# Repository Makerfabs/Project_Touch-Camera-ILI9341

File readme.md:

# Touch Screen Camera ILI9341

```c++
/*
Version:		V1.4
Author:			Vincent
Create Date:	2020/9/28
Note:
		V1.1:Add Screen Shot Receiver Function.
		V1.2:Add a faster camera example.
		2020/12/2 v1.3:Add album and a meter display.
		2020/12/28 v1.4: Add camera_faster_v2.
	
*/
```

[toc]

# OVERVIEW

## Introduce

[Makerfabs home page](https://www.makerfabs.com/)

[Makerfabs Wiki](https://wiki.makerfabs.com/)

The realization of a simple digital camera, you can take pictures through the camera framing. It is displayed on the TFT screen and provides touch options. Photos taken can be saved on an SD card.

The ILI9341 screen has more adaptation libraries. Such as Adafruit_GFX, Adafriut_ILI9341, TFT_eSPI and other libraries. The resistance screen is driven by Adafruit_STMPE610 library. Fully compatible with Adafruit products.

## Equipment list

- ESP32 Touch Camera ILI9341
- Micro SD card

# ESP32 Touch Camera

## Product link ：[ESP32 3.2" TFT Touch with Camera](https://www.makerfabs.com/esp32-3.2-inch-tft-touch-with-camera.html) 

The ESP32 Touch Camera ILI9341 use ILI9341 screen, which comes with resistive screens. Have an OV2640 camera and SD card slot. It can be used as a webcam, an electronic album, or a digital camera. Support for Arduino and MicroPython. 

## Feature

- Integrated ESP32 2.4G WiFi and Bluetooth.
- Micro SD card slot on board.
- Input 5.0V Type-C USB .
- OV2640 is a 1/4 inch CMOS UXGA (1632*1232) image sensor manufactured by OmniVision.
- LCD 3.2 inch Amorphous-TFT-LCD (Thin Film Transistor Liquid Crystal Display) for mobile-phone or handy electrical equipments. The resolution is 320*240.
- STMPE610 is A 4-wire resistive touch screen control circuit with I2C interface and SPI interface.

# Example

## Camera

This is a test demo. You can check that ESP32, screen, touch, SD card reader and the camera function properly.

- Copy logo.bmp to sd card.
- Insert SD card.
- Upload code to ESP32.
- Restart ESP32.
- Screen will show "TOUCH TO START TEST", please touch screen.
- Will show logo picture in SD card.
- And ESP32 will open camera, and show on screen.

### Camera_faster_v2

Use LovyanGFX library. More faster than Adafruit_GFX. This example don't need SD card.
- Upload code to ESP32.
- Copy logo320240.bmp to sd card.
- Insert SD card.
- Restart ESP32.
- Screen will show "TOUCH TO START TEST", please touch screen.
- And ESP32 will open camera, and show on screen.

## Example introduction

Five projects were implemented : "Graphic_Test", "Touch_Test", "Touch_Draw", "SD_Test" and "Wifi_Camera".

### Graphic_Test

- Test ILI9341 screen with Adafruit_ILI9341 library.

### Touch_Draw

- Test ILI9341 screen with Adafruit_STMPE610 library.

### Touch_Draw

- Use your hand or stylus (resistance screen) to draw on the screen.

### SD_Test

- Display pictures from SD card.

### Wifi_Camera

- Use esp32 and ov2640 as a webcam.
- Provides a real-time display of the control web page.

### Screen Shot Receiver

Transmit the contents of the monitor to the TFT screen via Wifi.A host computer software is provided to box select the areas of the screen that need to be transferred.

Change from [MakePython ESP32 Color LCD で 動画をWiFi受信](https://homemadegarbage.com/makerfabs05)

- Upload codes.

- Open "ScreenShotSender.exe"

- Input IP on the screen.

- Click "Connect"

  `
### Album

Read JPG image from SD card and display it on screen.You can switch photos by clicking on the left or right side of the screen.For the sake of display, it is best not to be larger than 320 * 240 pixels.
- Copy the image from the JPG folder to the SD root directory.
- Insert SD card.
- Upload code to ESP32.
- Restart ESP32.
- Will show jpg picture in SD card.

## Compiler Options

**If you have any questions，such as how to install the development board, how to download the code, how to install the library. Please refer to :[Makerfabs_FAQ](https://github.com/Makerfabs/Makerfabs_FAQ)**

- Install board : ESP32 .
- Install library : Adafruit_GFX library.
- Install library : Adafruit_ILI9341 library.
- Install library : Adafruit_STMPE610 library.

- Insert a Micro SD card into ESP32 Touch Camera.
- Upload codes, select "ESP32 Wrover Module" and "Huge APP"

## Code Explain

- Import Library

```c++
#include "SPI.h"
#include "SD.h"
#include "FS.h"
#include "Adafruit_STMPE610.h"
#include "Adafruit_GFX.h"
#include "Adafruit_ILI9341.h"
```

- Define Pins

```c++
//SPI
#define SPI_MOSI 13
#define SPI_MISO 12
#define SPI_SCK 14

//SD Card
#define SD_CS 4

//Touch Screen
#define STMPE_CS 2

//TFT
#define TFT_CS 15
#define TFT_DC 33
#define TFT_LED -1 //1//-1
#define TFT_RST -1 //3//-1
```

- Set Cs function. Because the screen, touch and SD card all use SPI interface. To prevent SPI conflicts, the manual SPI switch is set. Low is enable.

```c++
//SPI control
#define SPI_ON_TFT digitalWrite(TFT_CS, LOW)
#define SPI_OFF_TFT digitalWrite(TFT_CS, HIGH)
#define SPI_ON_SD digitalWrite(SD_CS, LOW)
#define SPI_OFF_SD digitalWrite(SD_CS, HIGH)
#define STMPE_ON digitalWrite(STMPE_CS, LOW)
#define STMPE_OFF digitalWrite(STMPE_CS, HIGH)
```

- Init SPI

```c++
SPI.begin(SPI_SCK, SPI_MISO, SPI_MOSI);
```

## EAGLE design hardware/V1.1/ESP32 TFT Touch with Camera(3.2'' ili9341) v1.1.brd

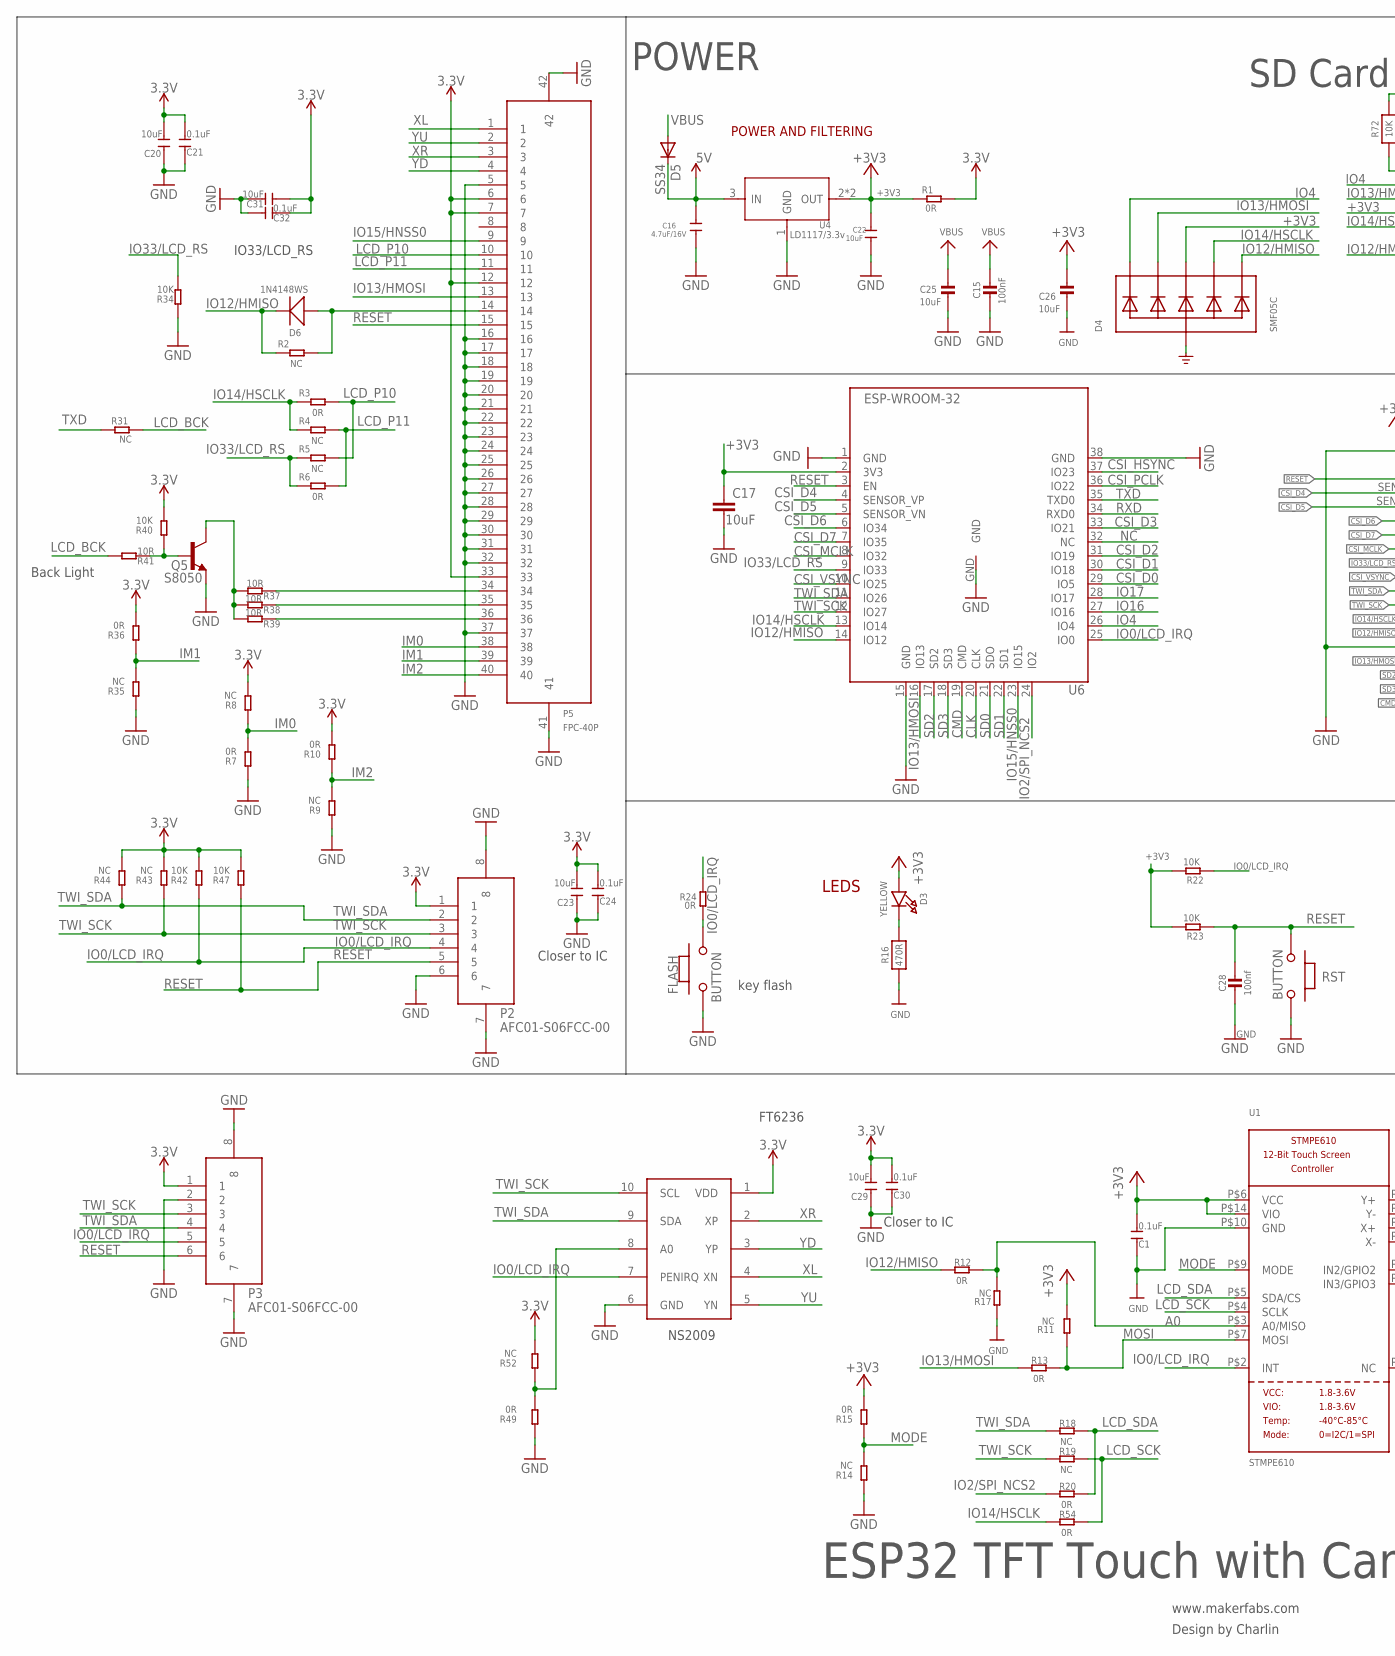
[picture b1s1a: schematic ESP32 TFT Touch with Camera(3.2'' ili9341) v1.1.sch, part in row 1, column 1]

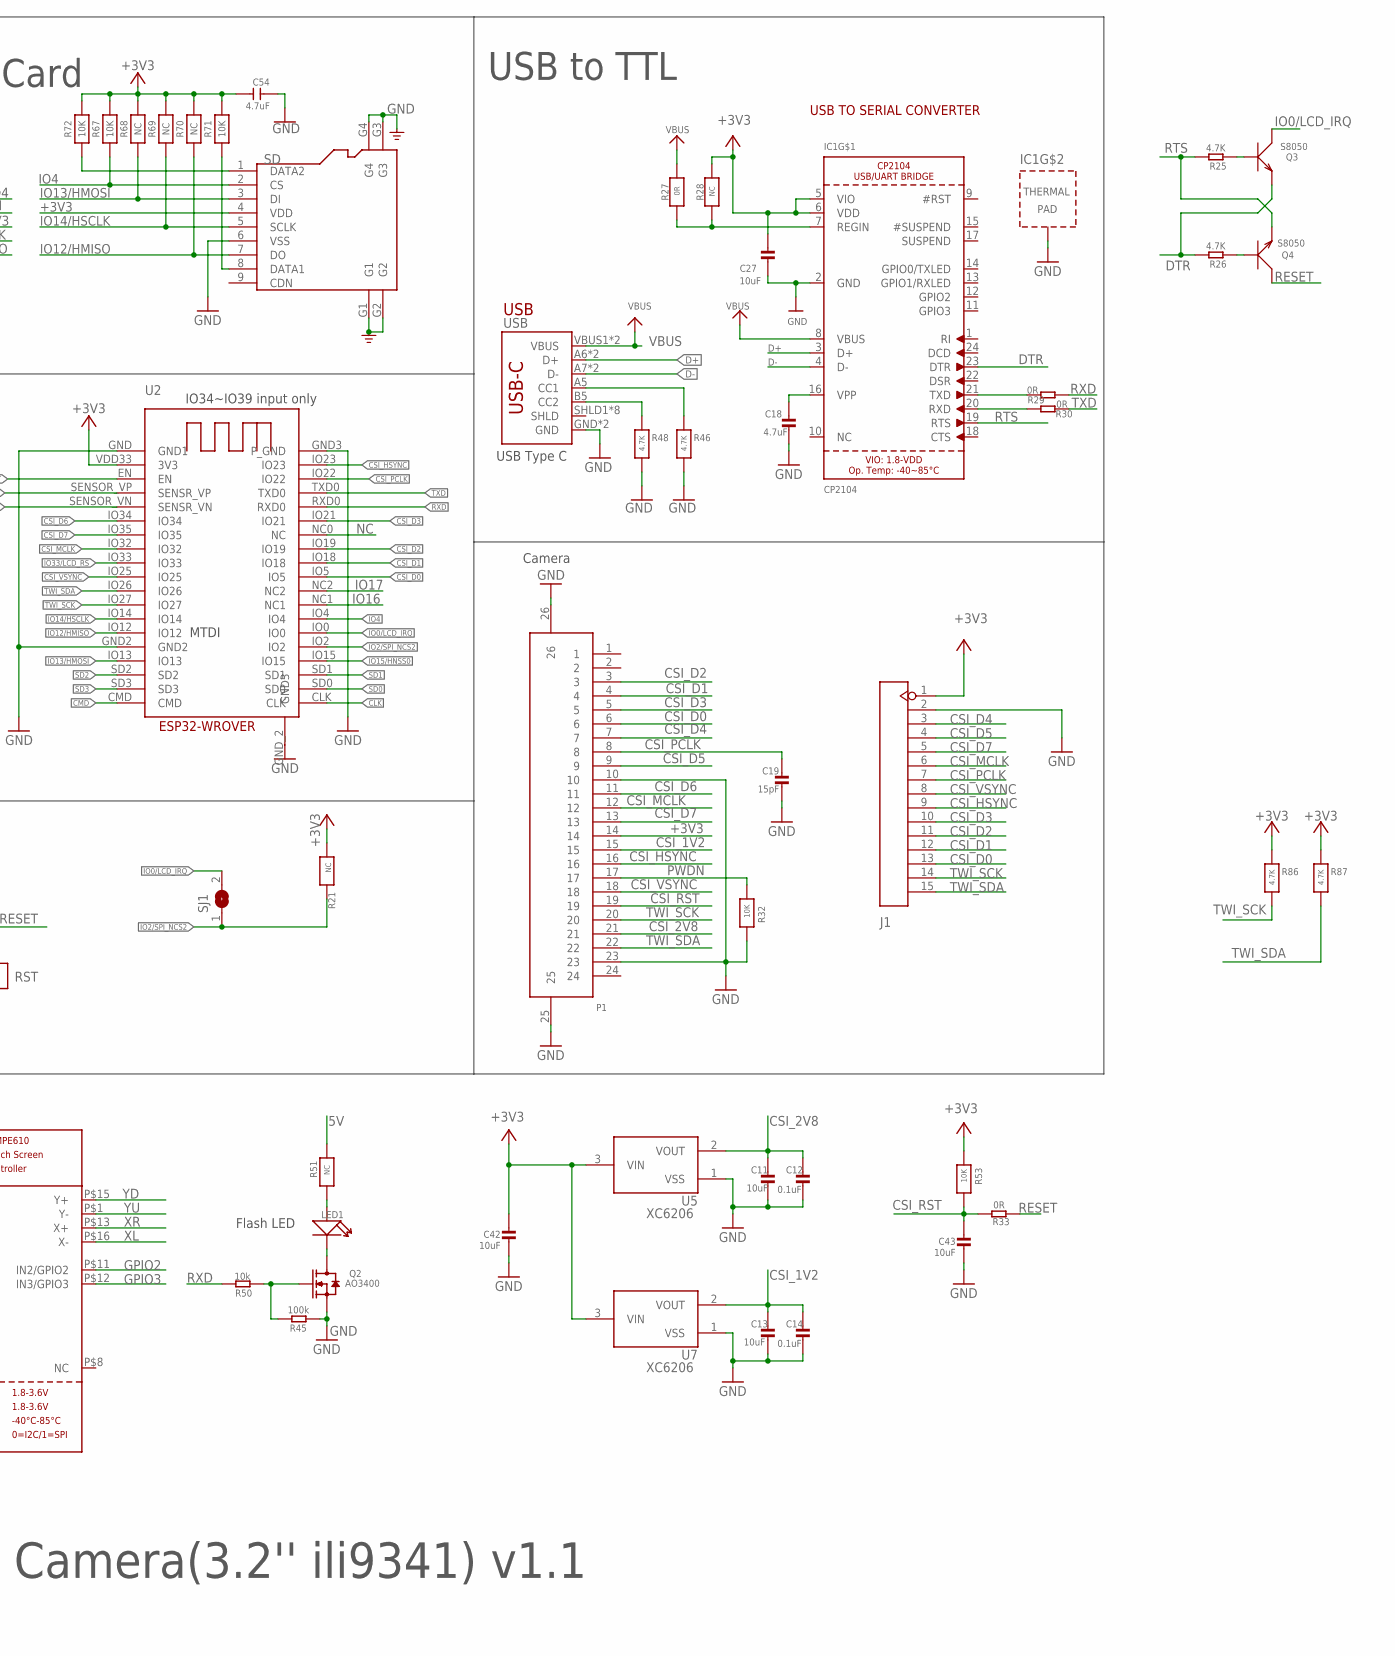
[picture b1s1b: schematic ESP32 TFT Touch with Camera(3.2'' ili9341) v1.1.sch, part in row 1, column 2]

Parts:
C1, C21, C24, C30, C32: 0.1uF; DISCRETE_C0603
C11, C13, C25, C26, C27, C42, C43: 10uF; 0603-NO
C12, C14: 0.1uF; 0603-NO
C15: 100nF; 0603-NO
C16: 4.7uF/16V; 0603
C17: 10uF; C0603
C18: 4.7uF; 0603-NO
C19: 15pF; 0603-NO
C20, C23, C29, C31: 10uF; DISCRETE_C0603
C22: 10uF; 0603
C28: 100nf; 0603-NO
C54: 4.7uF; DISCRETE_C0603
D3: YELLOW; CHIPLED_0805_NOOUTLINE
D4: SMF05C; SOT363
D5: SS34; DO-214AC
D6: 1N4148WS; SOD323
FLASH: BUTTON; 157SW
IC1: CP2104; QFN24_4MM_SMSC
J1: HEADER-1X15P; SMD15-2.54P8.5H
LED1: DISCRETE_LED3528; DISCRETE_LED-3528
P1: FPC-24P; SMD26-50P-1760L450W
P2, P3: AFC01-S06FCC-00; SMD8-50P-740L535W
P5: FPC-40P; SMD42-50P-2560L490W
Q2: AO3400; SOT23@1
Q3, Q4: S8050; SOT23
Q5: S8050; SPARKFUN_SOT23
R1, R3, R6, R12, R13, R20, R24, R29, R30, R33, R54: 0R; R0603
R2, R4, R5, R18, R19, R31: NC; R0603
R7, R10, R15, R36, R49: 0R; DISCRETE_R0603
R8, R9, R11, R14, R17, R35, R43, R44, R52: NC; DISCRETE_R0603
R16: 470R; 0603-NO
R21, R28, R51, R68, R69, R70: NC; 0603-NO
R22, R23: 10K; R0603
R25, R26: 4.7K; R0603
R27: 0R; 0603-NO
R32, R53, R67, R71, R72: 10K; 0603-NO
R34, R40, R42, R47: 10K; DISCRETE_R0603
R37, R38, R39, R41: 10R; DISCRETE_R0603
R45: 100k; R0603
R46, R48, R86, R87: 4.7K; 0603-NO
R50: 10k; R0603
RST: BUTTON; 157SW
SD: HOLDER-MICROSD-9P; 9P-SMD-W/-RING
SJ1: SJ
U1: STMPE610; QFN16_3MM
U2: ESP32-WROVER
U4: LD1117/3.3v; SOT89
U5, U7: XC6206; SOT-23
U6: ESP-WROOM-32
U8: NS2009; MSOP10
USB: USB_C5; USB-C-16P-5

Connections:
3.3V: C20.2, C21.2, C23.2, C24.2, C29.2, C30.2, C31.1, C32.1, P2.1, P3.1, P5.6, P5.7, P5.12, P5.33, R1.2, R8.2, R10.2, R36.2, R40.2, R42.2, R43.2, R44.2, R47.2, R52.2, U8.1 (VDD)
5V: C16.1, D5.C, R51.1, U4.3 (IN)
+3V3: C1.2, C17.1, C22.1, C26.1, C27.1, C42.1, C54.2, D3.A, D4.4 (C3), IC1.5 (VIO), IC1.6 (VDD), J1.1, P1.14, R1.1, R11.2, R15.2, R21.1, R22.2, R23.2, R28.1, R53.1, R67.2, R68.2, R69.2, R70.2, R71.2, R72.2, R86.1, R87.1, SD.4 (VDD), U1.P$6 (VCC), U1.P$14 (VIO), U2.VDD33 (3V3), U4.2 (OUT), U4.4 (OUT), U5.3 (VIN), U6.2 (3V3), U7.3 (VIN)
A0: R12.2, R17.2, U1.P$3 (A0/MISO)
CLK: U2.CLK, U6.20 (CLK)
CMD: U2.CMD, U6.19 (CMD)
CSI_1V2: C13.1, C14.1, P1.15, U7.2 (VOUT)
CSI_2V8: C11.1, C12.1, P1.21, U5.2 (VOUT)
CSI_D0: J1.13, P1.6, U2.IO5, U6.29 (IO5)
CSI_D1: J1.12, P1.4, U2.IO18, U6.30 (IO18)
CSI_D2: J1.11, P1.3, U2.IO19, U6.31 (IO19)
CSI_D3: J1.10, P1.5, U2.IO21, U6.33 (IO21)
CSI_D4: J1.3, P1.7, U2.SENSOR_VP (SENSR_VP), U6.4 (SENSOR_VP)
CSI_D5: J1.4, P1.9, U2.SENSOR_VN (SENSR_VN), U6.5 (SENSOR_VN)
CSI_D6: P1.11, U2.IO34, U6.6 (IO34)
CSI_D7: J1.5, P1.13, U2.IO35, U6.7 (IO35)
CSI_HSYNC: J1.9, P1.16, U2.IO23, U6.37 (IO23)
CSI_MCLK: J1.6, P1.12, U2.IO32, U6.8 (IO32)
CSI_PCLK: C19.1, J1.7, P1.8, U2.IO22, U6.36 (IO22)
CSI_RST: C43.1, P1.19, R33.2, R53.2
CSI_VSYNC: J1.8, P1.18, U2.IO25, U6.10 (IO25)
D+: IC1.3 (D+), USB.A6 (D+), USB.B6 (D+)
D-: IC1.4 (D-), USB.A7 (D-), USB.B7 (D-)
DTR: IC1.23 (DTR), Q3.2 (E), R26.2
GND: C1.1, C11.2, C12.2, C13.2, C14.2, C15.2, C16.2, C17.2, C18.2, C19.2, C20.1, C21.1, C22.2, C23.1, C24.1, C25.2, C26.2, C27.2, C28.2, C29.1, C30.1, C31.2, C32.2, C42.2, C43.2, C54.1, D4.2 (A), FLASH.1, IC1.2 (GND), IC1.THERM (TP), J1.2, P1.10, P1.23, P1.25, P1.26, P2.6, P2.7, P2.8, P3.2, P3.7, P3.8, P5.5, P5.16, P5.17, P5.18, P5.19, P5.20, P5.21, P5.22, P5.23, P5.24, P5.25, P5.26, P5.27, P5.28, P5.29, P5.30, P5.31, P5.32, P5.37, P5.41, P5.42, Q2.2 (S), Q5.2 (E), R7.1, R9.1, R14.1, R16.1, R17.1, R32.2, R34.1, R35.1, R45.1, R46.2, R48.2, R49.1, RST.1, SD.6 (VSS), SD.G1, SD.G2, SD.G3, SD.G4, U1.P$10 (GND), U2.GND (GND1), U2.GND2, U2.GND3 (P_GND), U2.GND_2 (GND3), U4.1 (GND), U5.1 (VSS), U6.1 (GND), U6.15 (GND), U6.38 (GND), U6.GND, U7.1 (VSS), U8.6 (GND), USB.GND, USB.GND2 (GND)
GPIO2: U1.P$11 (IN2/GPIO2)
GPIO3: U1.P$12 (IN3/GPIO3)
IM0: P5.38, R7.2, R8.1
IM1: P5.39, R35.2, R36.1
IM2: P5.40, R9.2, R10.1
IO0/LCD_IRQ: P2.4, P3.5, Q3.3 (C), R22.1, R24.2, R42.1, SJ1.2, U1.P$2 (INT), U2.IO0, U6.25 (IO0), U8.7 (PENIRQ)
IO2/SPI_NCS2: R20.1, R21.2, SJ1.1, U2.IO2, U6.24 (IO2)
IO4: D4.1 (C1), R67.1, SD.2 (CS), U2.IO4, U6.26 (IO4)
IO12/HMISO: D4.6 (C5), D6.-, R2.1, R12.1, R70.1, SD.7 (DO), U2.IO12, U6.14 (IO12)
IO13/HMOSI: D4.3 (C2), P5.13, R13.1, R68.1, SD.3 (DI), U2.IO13, U6.16 (IO13)
IO14/HSCLK: D4.5 (C4), R3.1, R4.1, R54.1, R69.1, SD.5 (SCLK), U2.IO14, U6.13 (IO14)
IO15/HNSS0: P5.9, U2.IO15, U6.23 (IO15)
IO16: U2.NC1, U6.27 (IO16)
IO17: U2.NC2, U6.28 (IO17)
IO33/LCD_RS: R5.1, R6.1, R34.2, U2.IO33, U6.9 (IO33)
LCD_BCK: R31.2, R41.2
LCD_P10: P5.10, R3.2, R5.2
LCD_P11: P5.11, R4.2, R6.2
LCD_SCK: R19.2, R54.2, U1.P$4 (SCLK)
LCD_SDA: R18.2, R20.2, U1.P$5 (SDA/CS)
MODE: R14.2, R15.1, U1.P$9 (MODE)
MOSI: R11.1, R13.2, U1.P$7 (MOSI)
unnamed: C18.1, IC1.16 (VPP)
unnamed: Q4.1 (B), R26.1
unnamed: Q3.1 (B), R25.1
unnamed: D6.+, P5.14, R2.2
unnamed: Q2.1 (G), R45.2, R50.1
unnamed: FLASH.2, R24.1
unnamed: D3.C, R16.2
unnamed: LED1.1 (+), R51.2
unnamed: LED1.2 (-), Q2.3 (D)
unnamed: R46.1, USB.A5 (CC1)
unnamed: R48.1, USB.B5 (CC2)
unnamed: IC1.7 (REGIN), R27.2, R28.2
unnamed: IC1.21 (TXD), R29.2
unnamed: IC1.20 (RXD), R30.2
unnamed: P5.34, R37.1
unnamed: P5.35, R38.1
unnamed: P5.36, R39.1
unnamed: Q5.1 (B), R40.1, R41.1
unnamed: Q5.3 (C), R37.2, R38.2, R39.2
unnamed: R49.2, R52.1, U8.8 (A0)
unnamed: R72.1, SD.1 (DATA2)
unnamed: R71.1, SD.8 (DATA1)
NC: U2.NC0 (NC), U6.32 (NC)
PWDN: P1.17, R32.1
RESET: C28.1, P2.5, P3.6, P5.15, Q4.3 (C), R23.1, R33.1, R47.1, RST.2, U2.EN, U6.3 (EN)
RTS: IC1.19 (RTS), Q4.2 (E), R25.2
RXD: R29.1, R50.2, U2.RXD0, U6.34 (RXD0)
SD0: U2.SD0, U6.21 (SDO)
SD1: U2.SD1, U6.22 (SD1)
SD2: U2.SD2, U6.17 (SD2)
SD3: U2.SD3, U6.18 (SD3)
TWI_SCK: J1.14, P1.20, P2.3, P3.3, R19.1, R43.1, R86.2, U2.IO27, U6.12 (IO27), U8.10 (SCL)
TWI_SDA: J1.15, P1.22, P2.2, P3.4, R18.1, R44.1, R87.2, U2.IO26, U6.11 (IO26), U8.9 (SDA)
TXD: R30.1, R31.1, U2.TXD0, U6.35 (TXD0)
VBUS: C15.1, C25.1, D5.A, IC1.8 (VBUS), R27.1, USB.VBUS1 (VBUS), USB.VBUS2 (VBUS)
XL: P5.1, U1.P$16 (X-), U8.4 (XN)
XR: P5.3, U1.P$13 (X+), U8.2 (XP)
YD: P5.4, U1.P$15 (Y+), U8.3 (YP)
YU: P5.2, U1.P$1 (Y-), U8.5 (YN)

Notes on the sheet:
www.makerfabs.com
Design by Charlin
USB
LEDS
POWER AND FILTERING
USB TO SERIAL CONVERTER
key flash
ESP32 TFT Touch with Camera(3.2'' ili9341) v1.1
MTDI
IO34~IO39 input only
POWER
USB to TTL
USB Type C
SD Card
Flash LED
Camera
NS2009
FT6236
Closer to IC
Back Light
IO33/LCD_RS

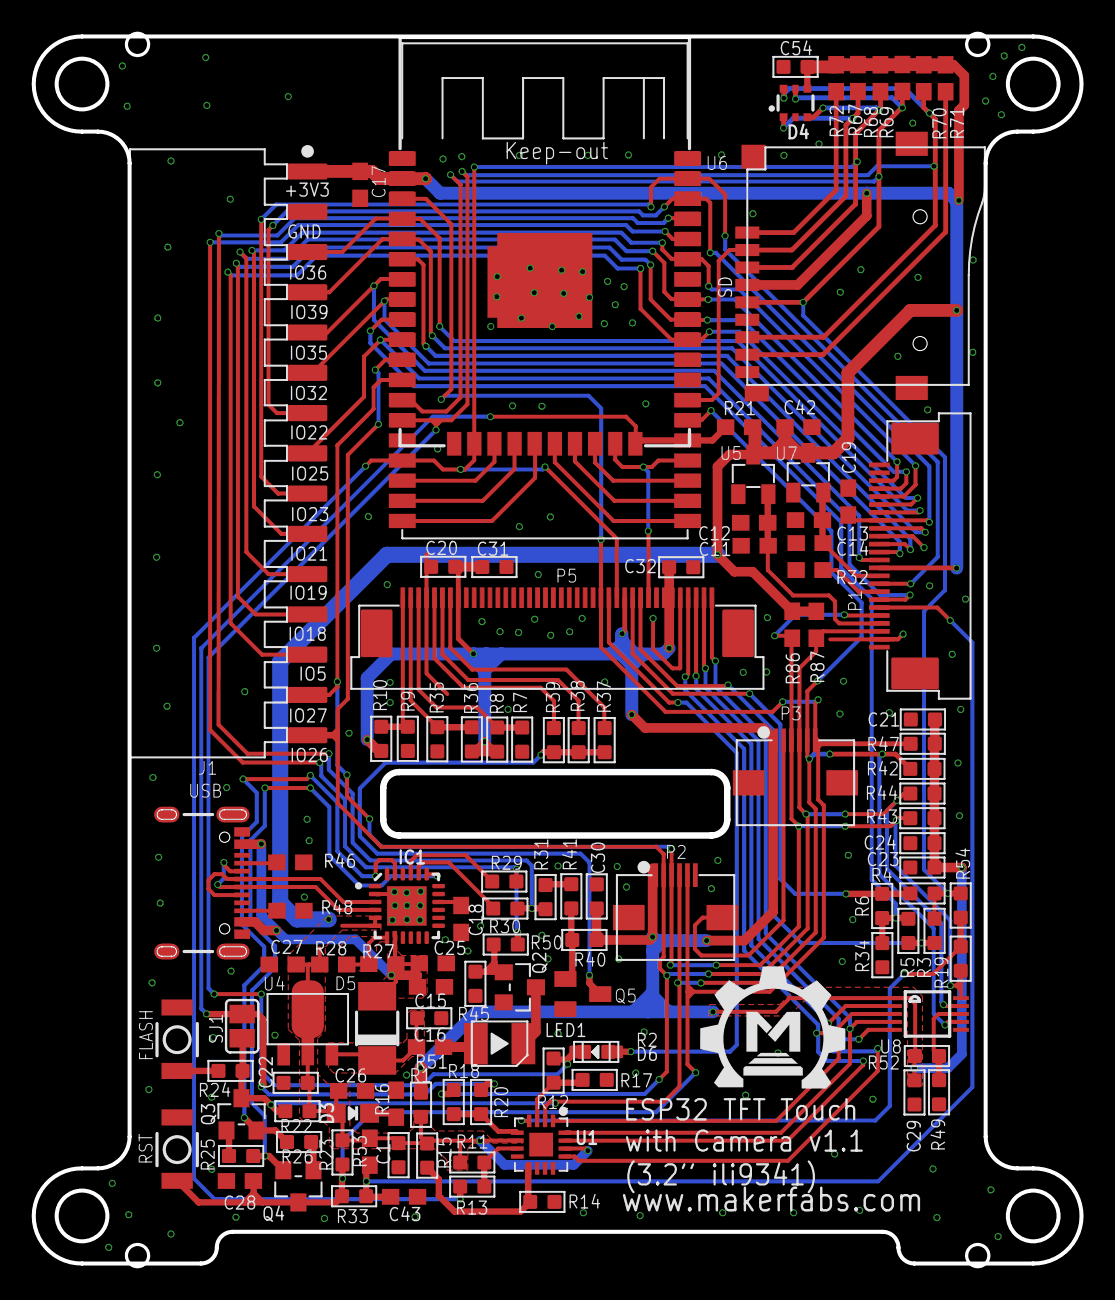
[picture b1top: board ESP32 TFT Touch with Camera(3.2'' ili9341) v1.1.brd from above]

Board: 2 copper layers, 66.1 x 77.4 mm, 116 parts (0 on the bottom side), 84 nets.

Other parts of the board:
U$1: MAKERFABS_0.3

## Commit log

2020-09-28 create project
2020-09-29 edit readme
2020-09-29 add test code
2020-10-12 Add Screen Shot Receiver
2020-11-11 Add faster camera
2020-11-23 add file
2020-12-02 Add album and meter display
2020-12-14 create
2020-12-28 Fix some bugs
2020-12-28 Add camera_faster_v2
2020-12-30 add files
2021-02-27 Fix pin name
2023-04-03 Add New Version LGFX demo

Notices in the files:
parts and their libraries:
microbuilder: This work is placed in the public domain, and may be freely used for commercial and non-commercial work with the following conditions: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
SparkFun-PowerSymbols: Licensing: Creative Commons ShareAlike 4.0 International - https://creativecommons.org/licenses/by-sa/4.0
